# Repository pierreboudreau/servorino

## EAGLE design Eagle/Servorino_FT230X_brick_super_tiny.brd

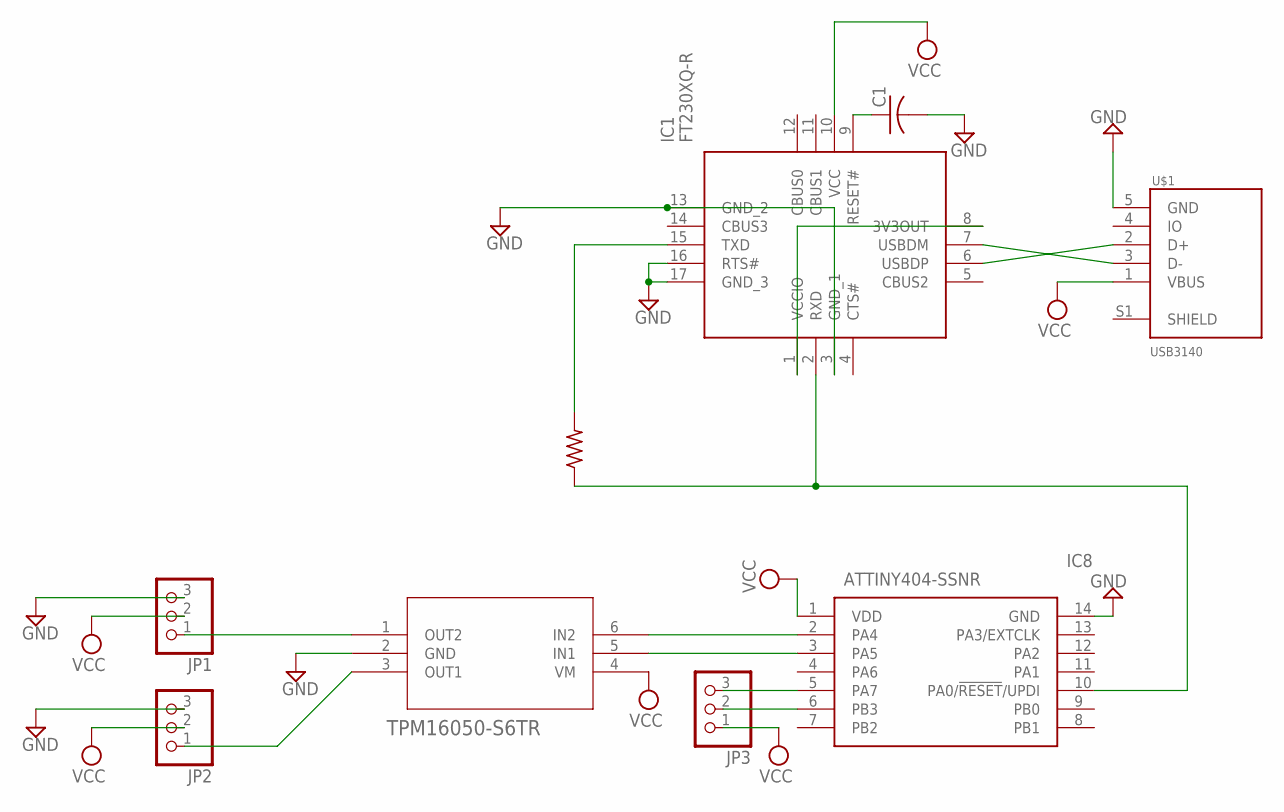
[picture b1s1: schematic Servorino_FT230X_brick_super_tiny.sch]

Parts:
C1: C-USC0603; C0603
IC1: FT230XQ-R; QFN65P400X400X80-17N
IC8: ATTINY404-SSNR; SOIC127P600X175-14N
JP1, JP2, JP3: PINHD-1X3; 1X03
R6: 470; R0805
U1: TPM16050-S6TR; SOT23-6_TPK
U$1: USB3140; USB3140-30-0170-0-C

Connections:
GND: C1.2, IC1.3 (GND_1), IC1.13 (GND_2), IC1.16 (RTS#), IC1.17 (GND_3), IC8.14 (GND), JP1.3, JP2.3, U1.2 (GND), U$1.5 (GND)
unnamed: IC8.2 (PA4), U1.6 (IN2)
unnamed: IC8.3 (PA5), U1.5 (IN1)
unnamed: JP1.1, U1.1 (OUT2)
unnamed: JP2.1, U1.3 (OUT1)
unnamed: IC1.1 (VCCIO), IC1.8 (3V3OUT)
unnamed: C1.1, IC1.9 (RESET#)
unnamed: IC1.7 (USBDM), U$1.3 (D-)
unnamed: IC1.6 (USBDP), U$1.2 (D+)
unnamed: IC8.5 (PA7), JP3.3
unnamed: IC8.6 (PB3), JP3.2
unnamed: IC1.15 (TXD), R6.2
unnamed: IC1.2 (RXD), IC8.10 (PA0/!RESET!/UPDI), R6.1
VCC: IC1.10 (VCC), IC8.1 (VDD), JP1.2, JP2.2, JP3.1, U1.4 (VM), U$1.1 (VBUS)

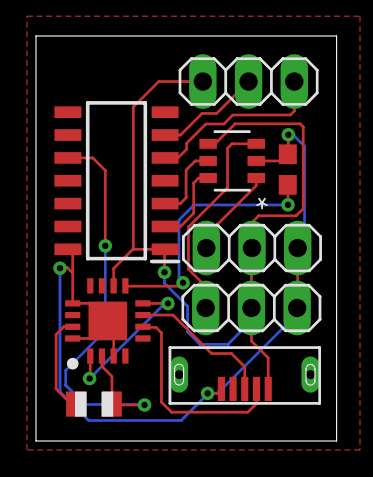
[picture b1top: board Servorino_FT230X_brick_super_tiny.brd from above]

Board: 2 copper layers, 16.7 x 22.5 mm, 9 parts (0 on the bottom side), 14 nets.

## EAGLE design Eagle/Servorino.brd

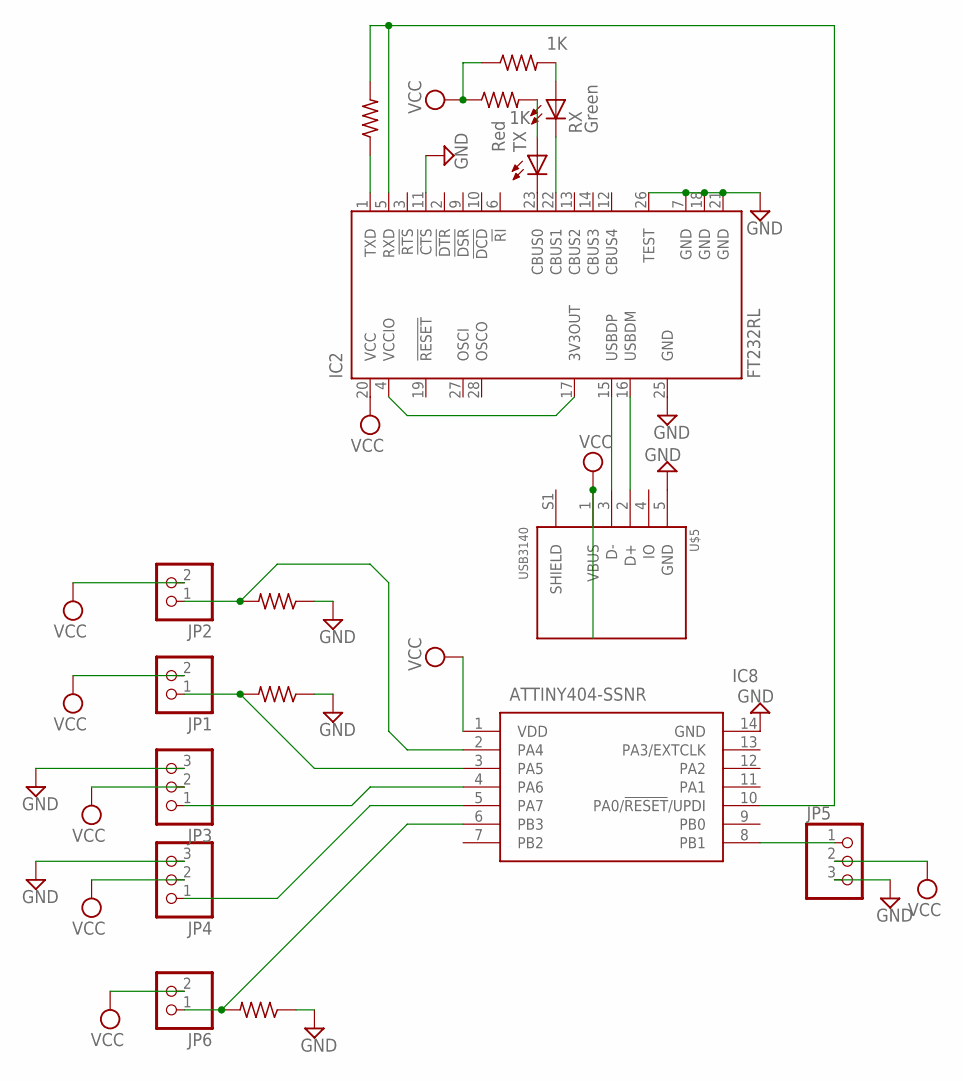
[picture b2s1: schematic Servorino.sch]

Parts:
IC2: FT232RL; SSOP28
IC8: ATTINY404-SSNR; SOIC127P600X175-14N
JP1, JP2, JP6: PINHD-1X2; 1X02
JP3, JP4, JP5: PINHD-1X3; 1X03
R1, R4, R5, R6: 470; R0805
R2, R3: 1K; R0805
RX: Green; CHIP-LED0805
TX: Red; CHIP-LED0805
U$5: USB3140; USB3140-30-0170-0-C

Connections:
GND: IC2.7 (GND), IC2.11 (!CTS), IC2.18 (GND), IC2.21 (GND), IC2.25 (GND), IC2.26 (TEST), IC8.14 (GND), JP3.3, JP4.3, JP5.3, R4.1, R5.1, R6.1, U$5.5 (GND)
unnamed: IC8.2 (PA4), JP2.1, R6.2
unnamed: IC8.6 (PB3), JP6.1, R4.2
unnamed: IC8.8 (PB1), JP5.1
unnamed: IC8.3 (PA5), JP1.1, R5.2
unnamed: IC8.4 (PA6), JP3.1
unnamed: IC8.5 (PA7), JP4.1
unnamed: IC2.16 (USBDM), U$5.2 (D+)
unnamed: IC2.15 (USBDP), U$5.3 (D-)
unnamed: IC2.4 (VCCIO), IC2.17 (3V3OUT)
unnamed: IC2.1 (TXD), R1.1
unnamed: IC2.5 (RXD), IC8.10 (PA0/!RESET!/UPDI), R1.2
unnamed: R2.2, RX.A
unnamed: R3.2, TX.A
unnamed: IC2.23 (CBUS0), TX.C
unnamed: IC2.22 (CBUS1), RX.C
VCC: IC2.20 (VCC), IC8.1 (VDD), JP1.2, JP2.2, JP3.2, JP4.2, JP5.2, JP6.2, R2.1, R3.1, U$5.1 (VBUS)

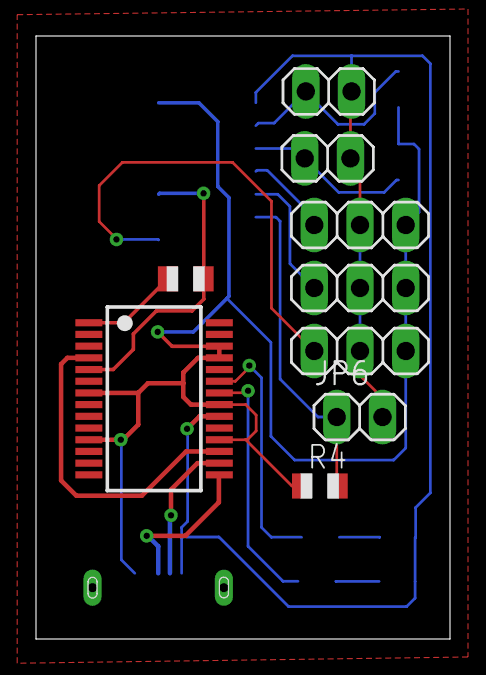
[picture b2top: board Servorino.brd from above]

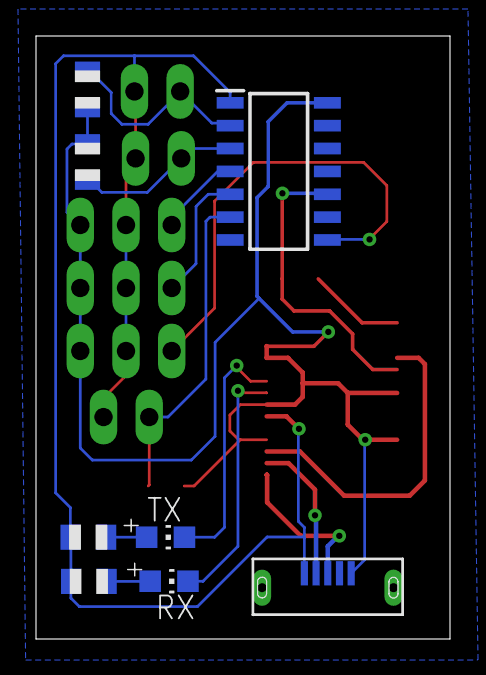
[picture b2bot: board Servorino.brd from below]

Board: 2 copper layers, 23.0 x 33.5 mm, 17 parts (8 on the bottom side), 17 nets.

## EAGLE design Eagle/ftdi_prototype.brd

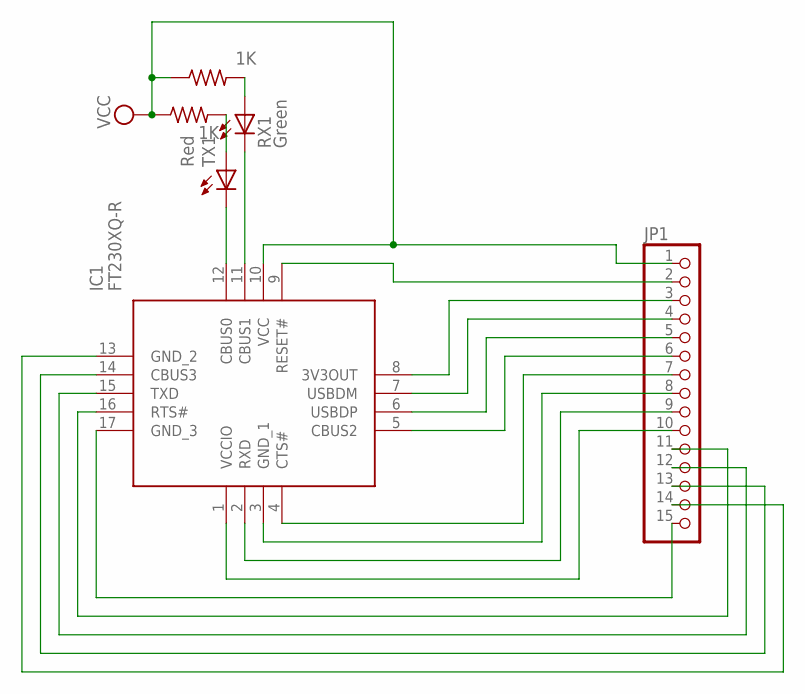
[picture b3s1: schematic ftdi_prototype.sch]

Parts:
IC1: FT230XQ-R; QFN65P400X400X80-17N
JP1: PINHD-1X15; 1X15
R4, R5: 1K; R0805
RX1: Green; CHIP-LED0805
TX1: Red; CHIP-LED0805

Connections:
unnamed: IC1.9 (RESET#), JP1.2
unnamed: IC1.5 (CBUS2), JP1.6
unnamed: IC1.6 (USBDP), JP1.5
unnamed: IC1.7 (USBDM), JP1.4
unnamed: IC1.8 (3V3OUT), JP1.3
unnamed: R4.2, RX1.A
unnamed: R5.2, TX1.A
unnamed: IC1.11 (CBUS1), RX1.C
unnamed: IC1.12 (CBUS0), TX1.C
unnamed: IC1.4 (CTS#), JP1.7
unnamed: IC1.3 (GND_1), JP1.8
unnamed: IC1.2 (RXD), JP1.9
unnamed: IC1.1 (VCCIO), JP1.10
unnamed: IC1.17 (GND_3), JP1.15
unnamed: IC1.16 (RTS#), JP1.11
unnamed: IC1.15 (TXD), JP1.12
unnamed: IC1.14 (CBUS3), JP1.13
unnamed: IC1.13 (GND_2), JP1.14
VCC: IC1.10 (VCC), JP1.1, R4.1, R5.1

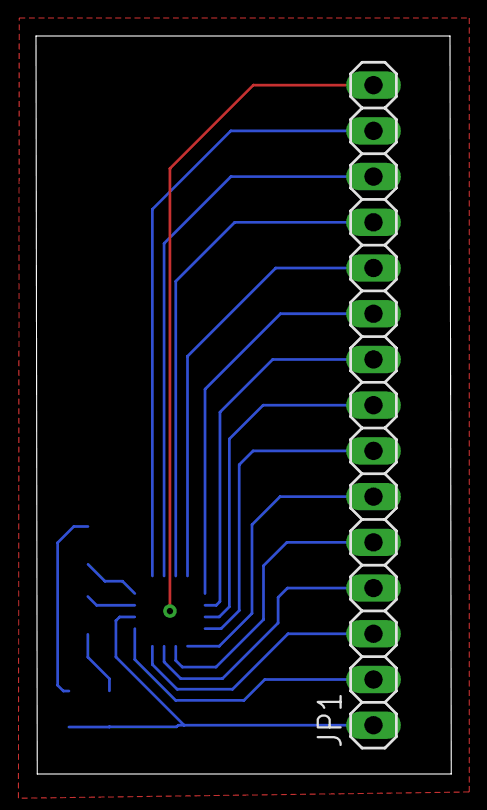
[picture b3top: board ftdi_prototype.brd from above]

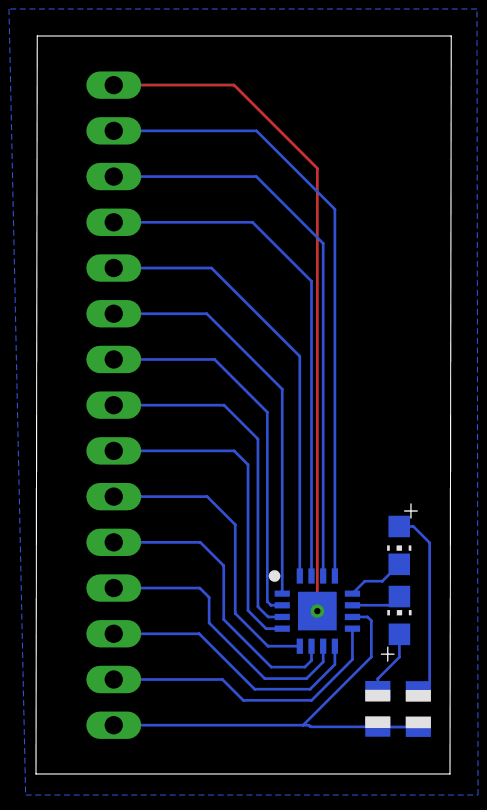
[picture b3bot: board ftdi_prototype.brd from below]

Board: 2 copper layers, 23.1 x 41.0 mm, 6 parts (5 on the bottom side), 19 nets.

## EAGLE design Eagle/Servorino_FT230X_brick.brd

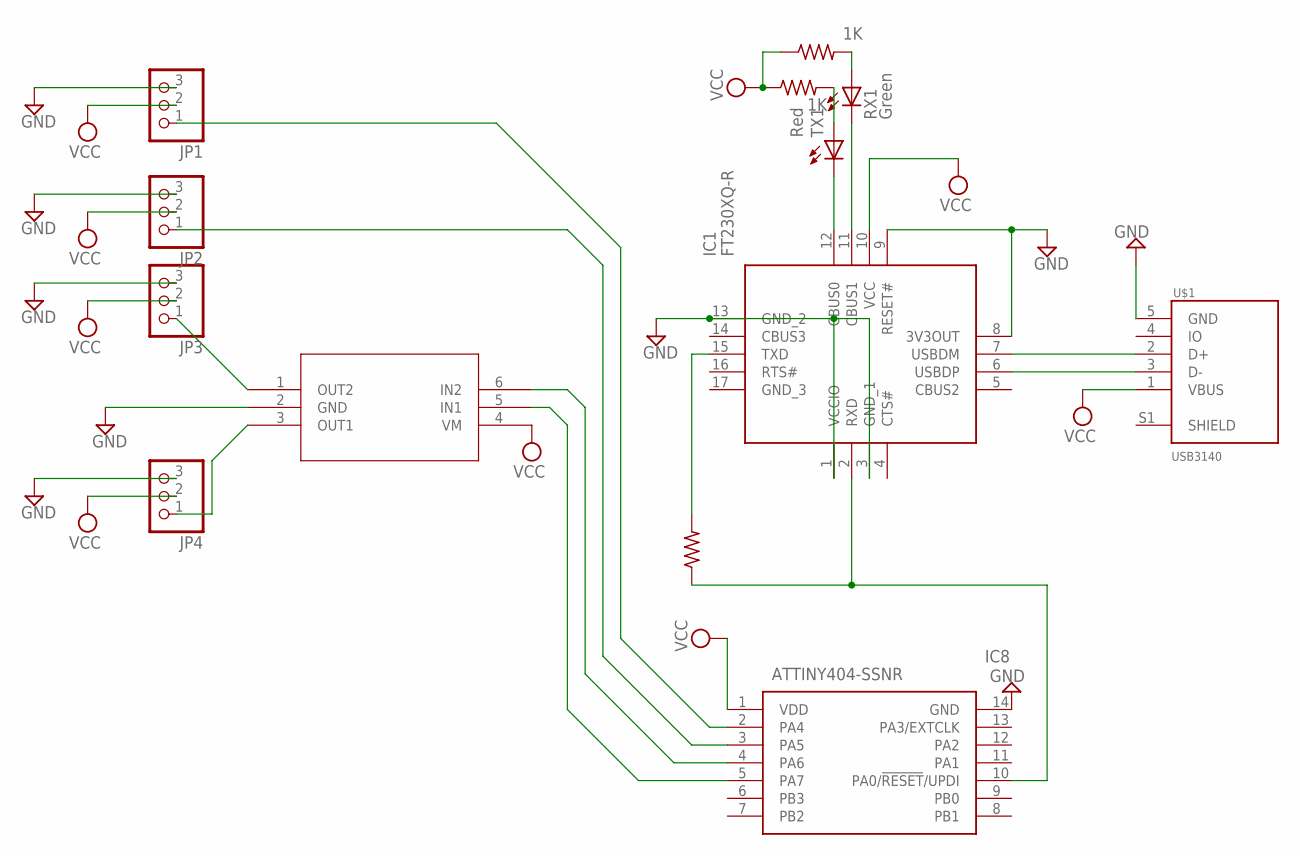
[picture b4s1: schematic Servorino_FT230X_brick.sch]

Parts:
IC1: FT230XQ-R; QFN65P400X400X80-17N
IC8: ATTINY404-SSNR; SOIC127P600X175-14N
JP1, JP2, JP3, JP4: PINHD-1X3; 1X03
R4, R5: 1K; R0805
R6: 470; R0805
RX1: Green; CHIP-LED0805
TX1: Red; CHIP-LED0805
U2: TPM16050-S6TRSOT23-6_TPK-L; SOT23-6_TPK-L
U$1: USB3140; USB3140-30-0170-0-C

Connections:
GND: IC1.1 (VCCIO), IC1.3 (GND_1), IC1.8 (3V3OUT), IC1.9 (RESET#), IC1.13 (GND_2), IC8.14 (GND), JP1.3, JP2.3, JP3.3, JP4.3, U2.2 (GND), U$1.5 (GND)
unnamed: IC8.2 (PA4), JP1.1
unnamed: IC8.4 (PA6), U2.6 (IN2)
unnamed: JP3.1, U2.1 (OUT2)
unnamed: IC8.3 (PA5), JP2.1
unnamed: IC8.5 (PA7), U2.5 (IN1)
unnamed: R4.2, RX1.A
unnamed: R5.2, TX1.A
unnamed: IC1.11 (CBUS1), RX1.C
unnamed: IC1.12 (CBUS0), TX1.C
unnamed: IC1.15 (TXD), R6.2
unnamed: IC1.6 (USBDP), U$1.3 (D-)
unnamed: IC1.2 (RXD), IC8.10 (PA0/!RESET!/UPDI), R6.1
unnamed: IC1.7 (USBDM), U$1.2 (D+)
unnamed: JP4.1, U2.3 (OUT1)
VCC: IC1.10 (VCC), IC8.1 (VDD), JP1.2, JP2.2, JP3.2, JP4.2, R4.1, R5.1, U2.4 (VM), U$1.1 (VBUS)

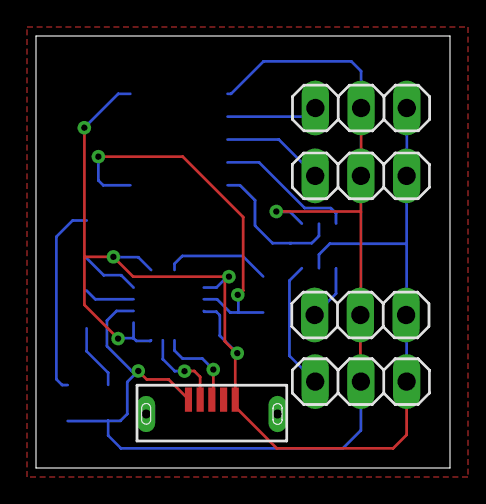
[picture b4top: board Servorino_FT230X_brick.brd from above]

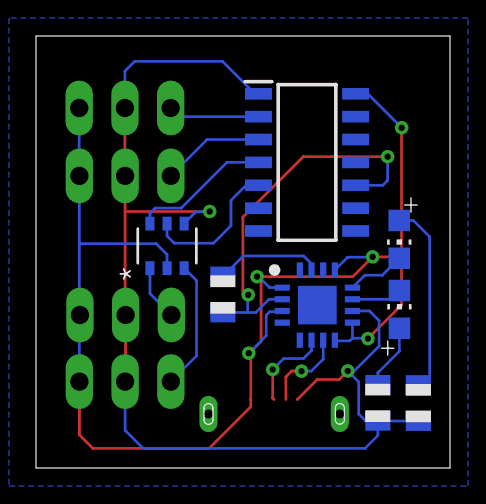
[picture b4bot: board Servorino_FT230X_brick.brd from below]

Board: 2 copper layers, 23.0 x 24.0 mm, 13 parts (8 on the bottom side), 16 nets.

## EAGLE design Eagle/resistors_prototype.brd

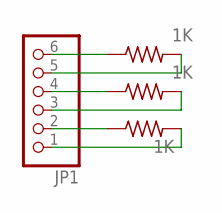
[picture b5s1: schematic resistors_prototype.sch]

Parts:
JP1: PINHD-1X6; 1X06
R2, R4, R5: 1K; R0805

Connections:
unnamed: JP1.6, R2.1
unnamed: JP1.5, R2.2
unnamed: JP1.4, R4.1
unnamed: JP1.3, R4.2
unnamed: JP1.2, R5.1
unnamed: JP1.1, R5.2

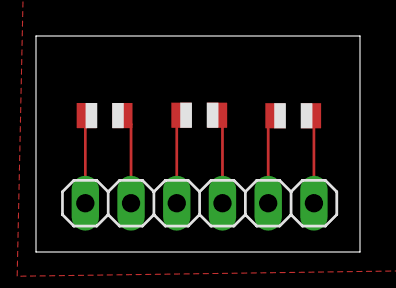
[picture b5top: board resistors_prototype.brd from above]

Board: 2 copper layers, 18.0 x 12.0 mm, 4 parts (0 on the bottom side), 6 nets.

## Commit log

2025-01-19 prototype boards
2025-01-19 missed one

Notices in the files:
parts and their libraries:
COPYRIGHT: Copyright (C) 2025 Ultra Librarian. All rights reserved.
